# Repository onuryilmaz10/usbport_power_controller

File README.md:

# usbport_power_controller
An arduino based product UPC allows you to manage the connection of your computer between usb powered device. You can control it remotely with serial communication software running on your system. 
Designed by Onur Yilmaz and Yusuf Arabaci. 

Contact mail: onr.yilmaz10@gmail.com

# Connection 
Detect CH340 in ComPorts list.
Baud Rate is 9600. After serial communication setup, connects if you send "C" (connect), disconnects if you send "D" (disconnect).

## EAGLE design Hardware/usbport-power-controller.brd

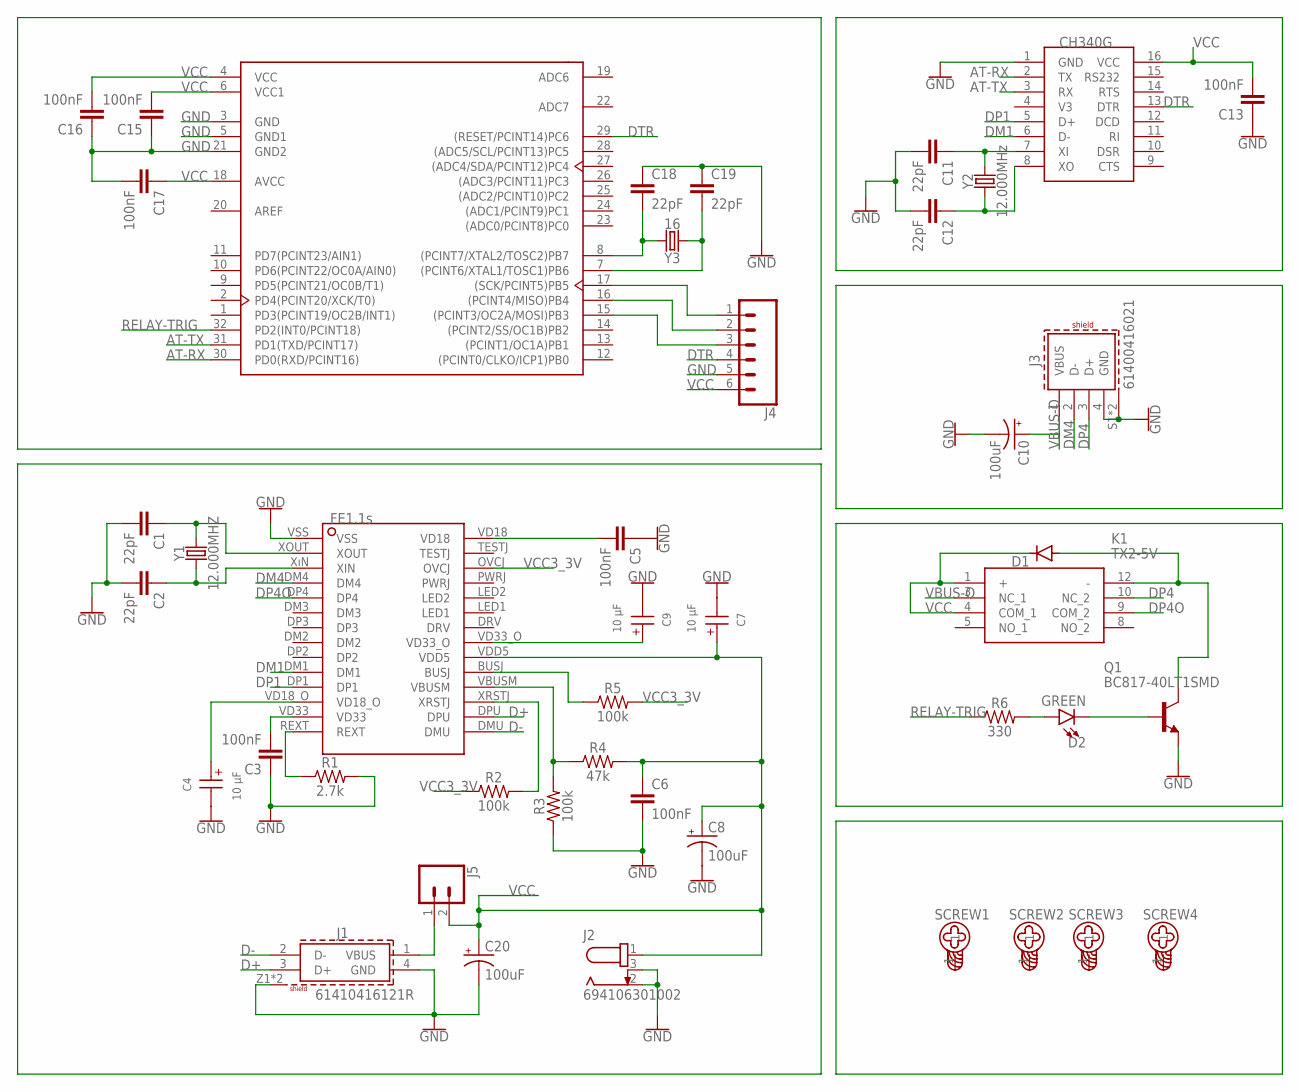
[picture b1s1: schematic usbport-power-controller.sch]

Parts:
ATMEGA328P-AU: ATMEGA328P-AU; TQFP-32
C1, C2, C11, C12, C18, C19: 22pF; 1206
C3, C5, C6, C13, C15, C16, C17: 100nF; 1206
C4, C7, C9: 10 µF; WCAP-ASLI_4X5.5(DXL)
C8, C10, C20: 100uF; PANASONIC_D
D1: DIODE-DO-214AC; DO-214AC
D2: GREEN; LED-1206
J1: 61410416121R
J2: 694106301002
J3: 61400416021
J4: CONN_06NO_SILK_FEMALE_PTH; 1X06_NO_SILK
J5: CONN_02; 1X02
K1: TX2-5V; TX2-24V
Q1: BC817-40LT1SMD; SOT23-BEC
R1: 2.7k; 1206
R2, R3, R5: 100k; 1206
R4: 47k; 1206
R6: 330; 1206
SCREW1, SCREW2, SCREW3, SCREW4: 4946
U$1: FE1.1S
U$2: CH340G; SOIC16
Y1: 12.000MHZ; HC49UP
Y2: 12.000MHz; HC49UP
Y3: 16; HC49UP

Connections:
AREF: ATMEGA328P-AU.20 (AREF)
AT-RX: ATMEGA328P-AU.30 (PD0(RXD/PCINT16)), U$2.2 (TX)
AT-TX: ATMEGA328P-AU.31 (PD1(TXD/PCINT17)), U$2.3 (RX)
D+: J1.3 (D+), U$1.DPU
D-: J1.2 (D-), U$1.DMU
DM1: U$1.DM1, U$2.6 (D-)
DM4: J3.2 (D-), U$1.DM4
DP1: U$1.DP1, U$2.5 (D+)
DP4: J3.3 (D+), K1.10 (NC_2)
DP4O: K1.9 (COM_2), U$1.DP4
DTR: ATMEGA328P-AU.29 ((RESET/PCINT14)PC6), J4.4, U$2.13 (DTR)
GND: ATMEGA328P-AU.3 (GND), ATMEGA328P-AU.5 (GND1), ATMEGA328P-AU.21 (GND2), C1.2, C2.2, C3.1, C4.2 (-), C5.1, C6.2, C7.2 (-), C8.-, C9.2 (-), C10.-, C11.2, C12.2, C13.1, C15.1, C16.1, C17.2, C18.1, C19.1, C20.-, J1.4 (GND), J1.Z1 (SHIELD), J1.Z2 (SHIELD), J2.2, J2.3, J3.4 (GND), J3.S1 (SHIELD), J3.S2 (SHIELD), J4.5, Q1.E, R1.2, R3.1, U$1.VSS, U$2.1 (GND)
unnamed: C2.1, U$1.XıN (XIN), Y1.1
unnamed: R2.2, U$1.XRSTJ
unnamed: R3.2, R4.1, U$1.VBUSM
unnamed: R1.1, U$1.REXT
unnamed: C1.1, U$1.XOUT, Y1.2
unnamed: C3.2, U$1.VD33
unnamed: R5.1, U$1.BUSJ
unnamed: D1.A, K1.12 (-), Q1.C
unnamed: C12.1, U$2.8 (XO), Y2.1
unnamed: C4.1 (+), U$1.VD18_O
unnamed: C11.1, U$2.7 (XI), Y2.2
unnamed: D2.C, Q1.B
unnamed: D2.A, R6.2
unnamed: ATMEGA328P-AU.8 ((PCINT7/XTAL2/TOSC2)PB7), C18.2, Y3.2
unnamed: ATMEGA328P-AU.17 ((SCK/PCINT5)PB5), J4.1
unnamed: ATMEGA328P-AU.7 ((PCINT6/XTAL1/TOSC1)PB6), C19.2, Y3.1
unnamed: ATMEGA328P-AU.16 ((PCINT4/MISO)PB4), J4.2
unnamed: ATMEGA328P-AU.15 ((PCINT3/OC2A/MOSI)PB3), J4.3
unnamed: J1.1 (VBUS), J5.1
unnamed: C5.2, U$1.VD18
RELAY-TRIG: ATMEGA328P-AU.32 (PD2(INT0/PCINT18)), R6.1
VBUS-O: C10.+, J3.1 (VBUS), K1.3 (NC_1)
VCC: ATMEGA328P-AU.4 (VCC), ATMEGA328P-AU.6 (VCC1), ATMEGA328P-AU.18 (AVCC), C6.1, C7.1 (+), C8.+, C13.2, C15.2, C16.2, C17.1, C20.+, D1.C, J2.1, J4.6, J5.2, K1.1 (+), K1.4 (COM_1), R4.2, U$1.VDD5, U$2.16 (VCC)
VCC3_3V: C9.1 (+), R2.1, R5.2, U$1.OVCJ, U$1.VD33_O

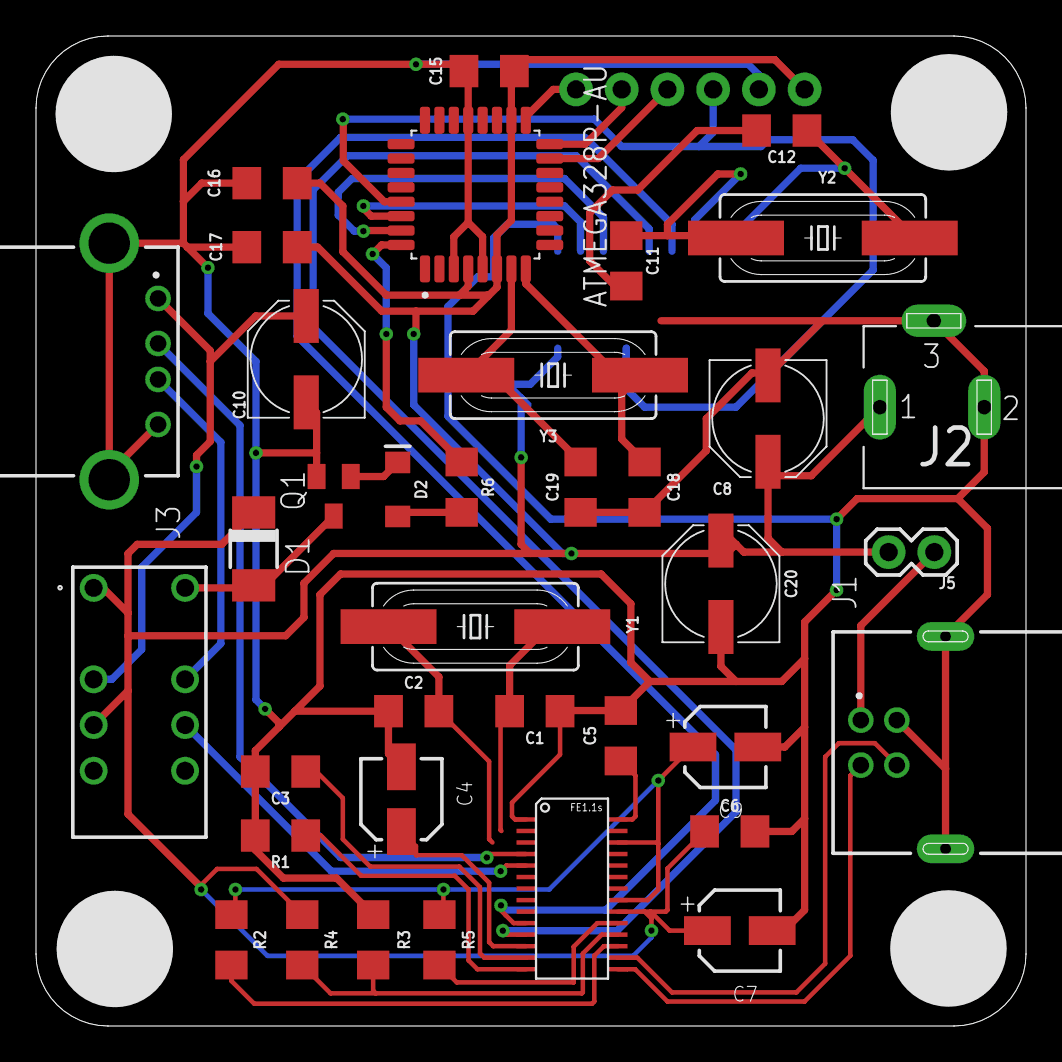
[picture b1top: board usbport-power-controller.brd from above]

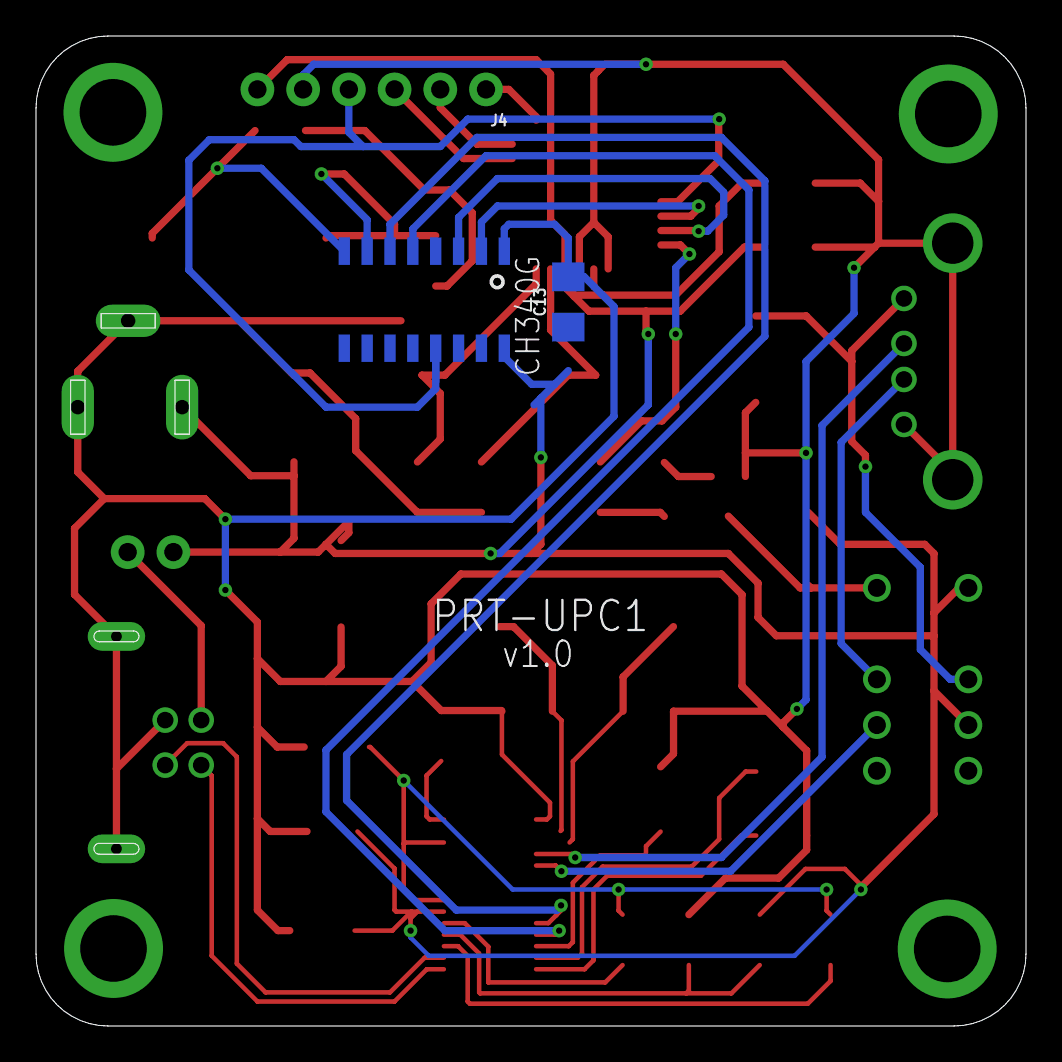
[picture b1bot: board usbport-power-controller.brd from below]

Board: 2 copper layers, 55.0 x 55.0 mm, 44 parts (3 on the bottom side), 35 nets.

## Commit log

2021-03-11 Create usb_power_controller_v1
2021-03-11 usb_power_controller_v1
2021-03-17 Update README.md
    Description
2021-03-17 Description
2021-03-17 Project description

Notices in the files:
parts and their libraries:
SparkFun-Clocks: Licensing: Creative Commons ShareAlike 4.0 International - https://creativecommons.org/licenses/by-sa/4.0
Wurth_Connectors_WR-USB: Copyright: Würth Elektronik
